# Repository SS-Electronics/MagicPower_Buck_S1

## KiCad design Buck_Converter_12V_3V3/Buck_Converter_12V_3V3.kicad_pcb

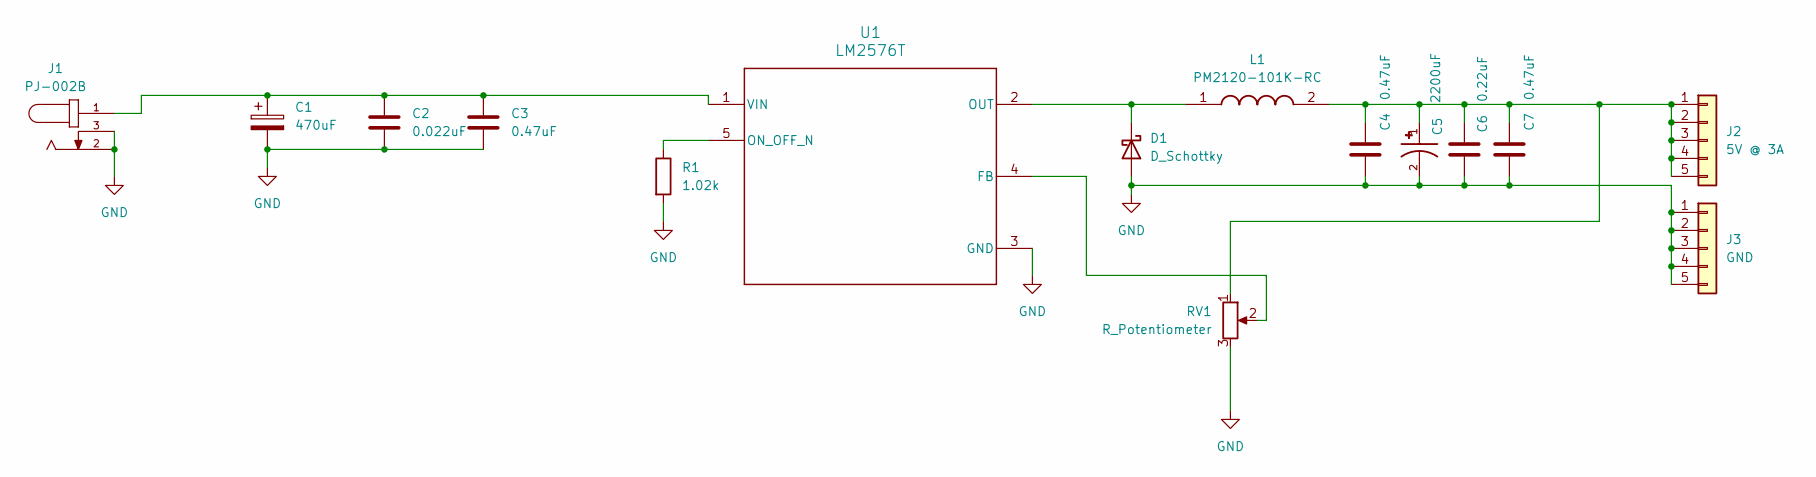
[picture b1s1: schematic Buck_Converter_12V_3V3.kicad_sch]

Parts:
C1: 470uF; CAP_EEVFK1J471M; Digikey Part# PCE3485CT-ND
C2: 0.022uF; C_0603_1608Metric_Pad1.08x0.95mm_HandSolder; Digikey Part# 445-173639-1-ND
C3, C4, C7: 0.47uF; C_1206_3216Metric_Pad1.33x1.80mm_HandSolder; Digikey Part# 445-6816-1-ND
C5: 2200uF; CAP_EEVFK1E222M; PARTREV 10-Oct-19; Digikey Part# PCE3463CT-ND
C6: 0.22uF; R_0603_1608Metric_Pad0.98x0.95mm_HandSolder; Digikey Part# 445-5191-1-ND
D1: D_Schottky; SMC_DIO-M; Digikey Part# B550C-FDICT-ND
J1: PJ-002B; CUI_PJ-002B; Digikey Part# CP-002B-ND
J2: 5V @ 3A; PinHeader_1x05_P2.54mm_Vertical
J3: GND; PinHeader_1x05_P2.54mm_Vertical
L1: PM2120-101K-RC; PM2120271KRC; Mouser Part Number 542-PM2120-101K-RC
R1: 1.02k; R_1206_3216Metric_Pad1.30x1.75mm_HandSolder; Digikey Part# 541-1.02KFCT-ND
RV1: R_Potentiometer; 601030_AVX; Digikey Part# 478-601030-ND
U1: LM2576T; LM2576xx; Digikey Part# LM2576T-ADJNS/NOPB-ND

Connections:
GND: C1.2, C2.2, C3.2, C4.2, C5.2, C6.2, C7.2, D1.2 (A), J1.2, J1.3, J3.1, J3.2, J3.3, J3.4, J3.5, R1.2, RV1.3, U1.3 (GND)
unnamed: D1.1 (K), L1.1, U1.2 (OUT)
unnamed: C4.1, C5.1, C6.1, C7.1, J2.1, J2.2, J2.3, J2.4, J2.5, L1.2, RV1.1
unnamed: RV1.2, U1.4 (FB)
unnamed: R1.1, U1.5 (ON_OFF_N)
unnamed: C1.1, C2.1, C3.1, J1.1, U1.1 (VIN)

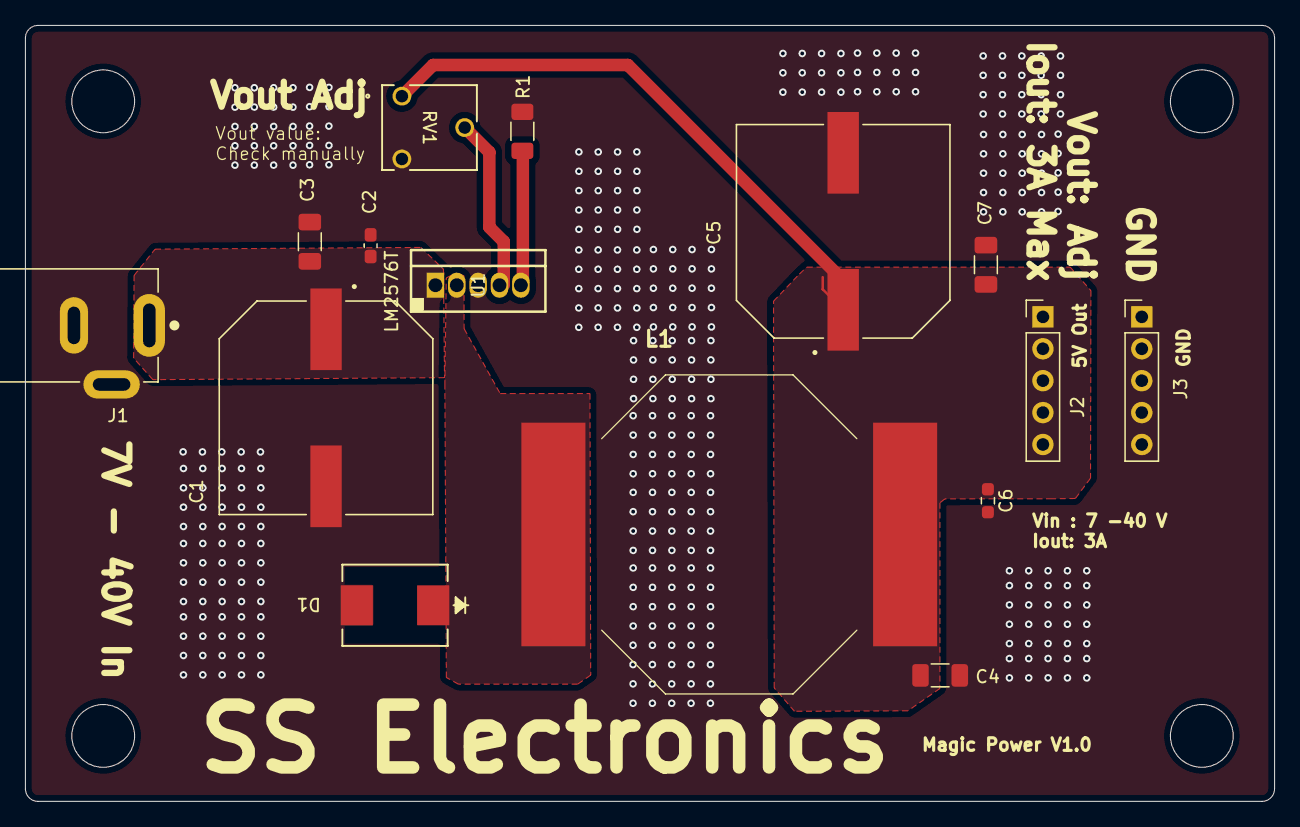
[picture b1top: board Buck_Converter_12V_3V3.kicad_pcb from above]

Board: 2 copper layers, 99.4 x 61.8 mm, 15 parts (0 on the bottom side), 6 nets.

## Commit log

2025-01-27 :tada: Blank KiCAD project created.
2025-01-28 :construction: Submodule added.
2025-01-28 :construction: POL IC and input cpacitors added.
2025-01-29 :construction: Inductor and cap added at power output.
2025-01-29 Layout Complete
    Vis Stiching pending.
2025-02-03 :rocket: Magicpower V1.0.0 Release
